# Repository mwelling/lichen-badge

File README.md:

# lichen-badge
Design files for the LICHEN Badge.

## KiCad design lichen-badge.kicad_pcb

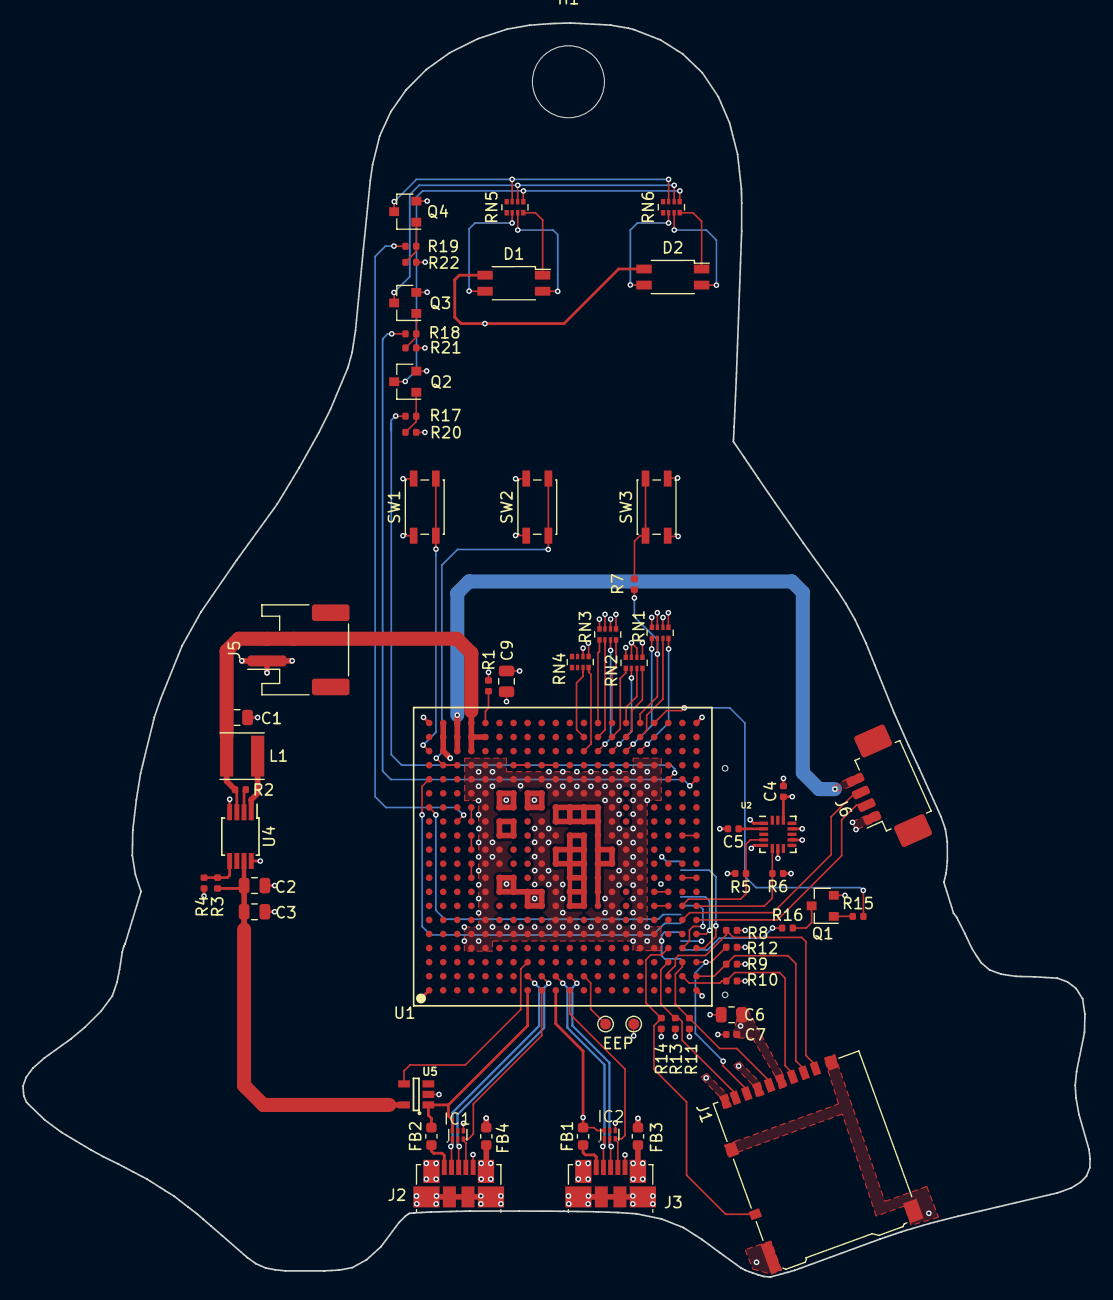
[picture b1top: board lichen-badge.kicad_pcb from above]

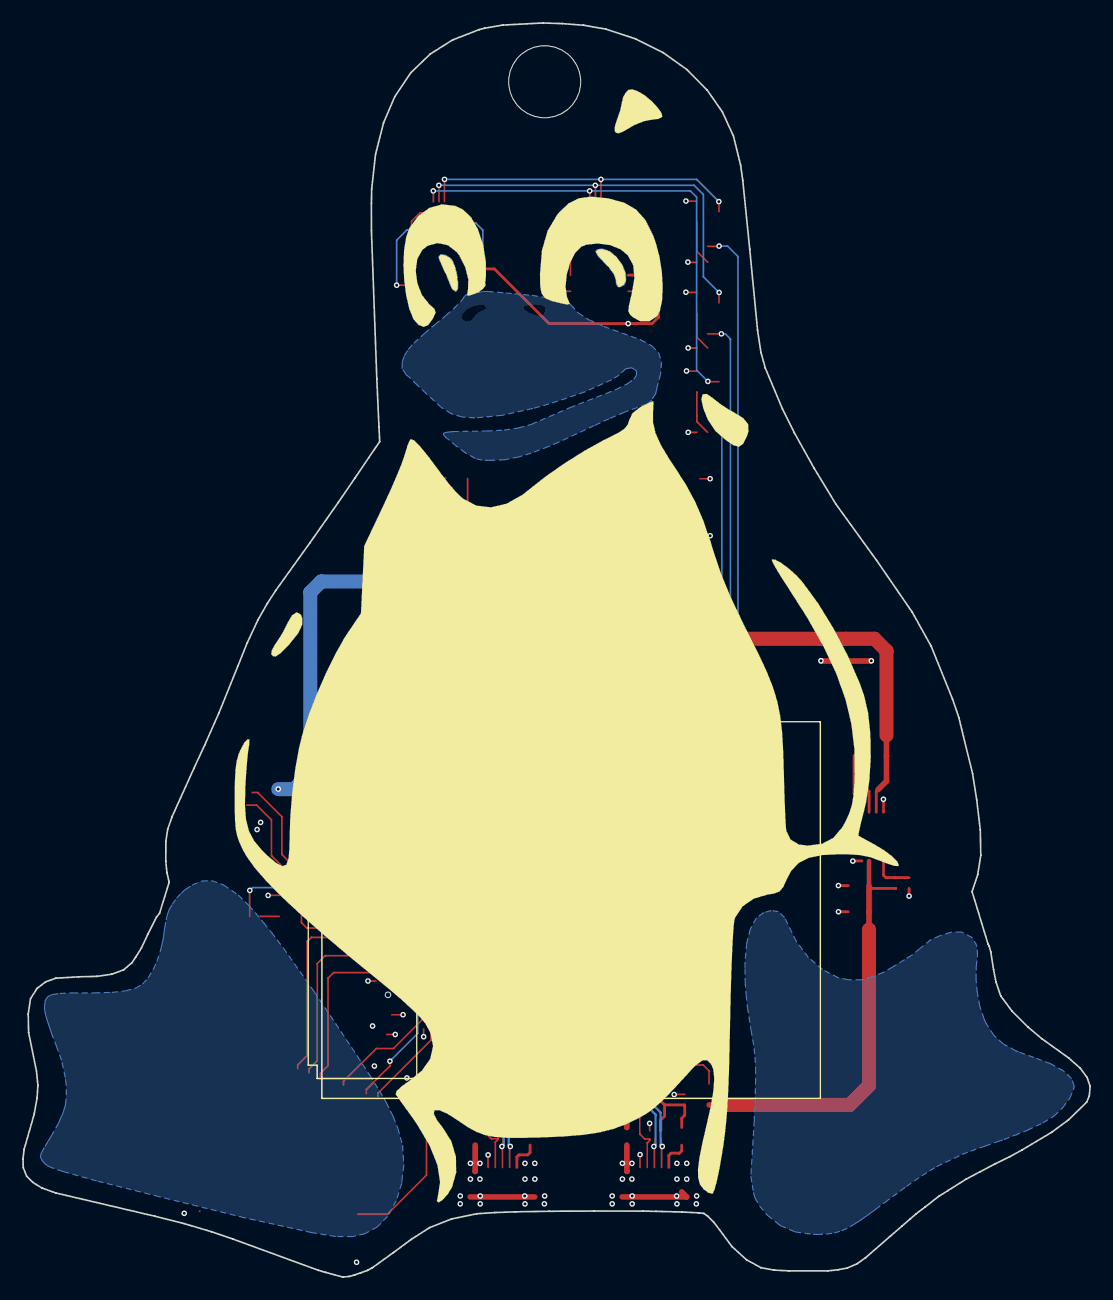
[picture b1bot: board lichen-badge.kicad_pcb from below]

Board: 4 copper layers, 96.3 x 113.2 mm, 66 parts (2 on the bottom side), 88 nets.

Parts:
C1, C2, C3: 22uF; C_0805_2012Metric
C4, C5, C7: .1uF; C_0402_1005Metric
C6: 10uF; C_0805_2012Metric
C9: 47uF; C_0805_2012Metric
D1, D2: LED_RABG; LED_SunLED_PLCC4_3.2x2.8mm_Reverse_Mount
FB1, FB2, FB3, FB4: Ferrite_Bead_Small; L_0603_1608Metric
H1: MountingHole; MountingHole_6.5mm
IC1, IC2: TPD4S012DRYR; SON-6(TI)-DRY
J1: Micro_SD_Card_Det; microSD_HC_Hirose_DM3AT-SF-PEJM5
J2, J3: USB_B_Micro; USB_Micro-B_Molex_47346-0001
J4, J7: TEST_1P; TestPoint_Pad_D1.0mm
J5: JST; JST_PH_S2B-PH-SM4-TB_1x02-1MP_P2.00mm_Horizontal
J6: Conn_01x04; Molex_PicoBlade_53261-0471_1x04-1MP_P1.25mm_Horizontal
L1: 2.2uH; L_Taiyo-Yuden_MD-4040
LOGO1: Logo_Open_Hardware_Small; tux-ghost
Q1, Q2, Q3, Q4: MMBT3904; SOT-23
R1: 10K; R_0402_1005Metric
R2, R3: 750K; R_0402_1005Metric
R4, R20, R21, R22: 100K; R_0402_1005Metric
R5, R6, R8, R9, R10, R11, R12, R13, R14, R17, R18, R19: 4.7K; R_0402_1005Metric
R7: 100; R_0402_1005Metric
R15: 470; R_0402_1005Metric
R16: 22; R_0402_1005Metric
RN1, RN2, RN3, RN4: 100K; R_Array_Convex_4x0402
RN5, RN6: 470; R_Array_Convex_4x0402
SW1: POWER; SW_SPST_EVQP2
SW2: RESET; SW_SPST_EVQP2
SW3: BOOT0; SW_SPST_EVQP2
U1: OSD335x-CSIP; BGA-400-1-27mm
U2: MMA8452QR1
U4: PAM2401SCADJ; MSOP-8_3x3mm_P0.65mm
U5: TPS2051C; SOT-23-5
X1: SPI-LCD-(1.8IN); LCD-(1.8IN)

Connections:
GND: C1.2, C2.2, C3.2, C4.2, C5.2, C6.2, C7.2, C9.2, FB3.2, FB4.2, IC1.4, IC2.4, J1.6, J1.9, J2.5, J3.5, J5.1, J6.1, J7.1, Q1.2, Q2.2, Q3.2, Q4.2, R1.2, R4.2, R20.2, R21.2, R22.2, RN1.5, RN1.6, RN2.6, RN2.7, RN2.8, RN3.5, RN3.6, RN3.7, RN3.8, RN4.5, RN4.6, SW1.1, SW2.1, SW3.2, U1.A1, U1.A20, U1.D4, U1.D5, U1.D15, U1.D16, U1.D17, U1.E4, U1.E5, U1.E6, U1.E7, U1.E8, U1.E9, U1.E10, U1.E11, U1.E12, U1.E13, U1.E14, U1.E15, U1.E16, U1.E17, U1.F5, U1.F10, U1.F11, U1.F16, U1.F17, U1.G5, U1.G16, U1.H5, U1.H16, U1.J5, U1.J9, U1.J10, U1.J11, U1.J12, U1.J13, U1.J16, U1.K5, U1.K6, U1.K7, U1.K8, U1.K9, U1.K12, U1.K15, U1.K16, U1.L5, U1.L6, U1.L15, U1.L16, U1.M5, U1.M15, U1.M16, U1.N5, U1.N6, U1.N15, U1.N16, U1.P5, U1.P6, U1.P7, U1.P8, U1.P9, U1.P12, U1.P13, U1.P14, U1.P15, U1.P16, U1.R5, U1.R9, U1.R10, U1.R11, U1.R12, U1.R16, U1.T4, U1.T5, U1.T6, U1.T7, U1.T8, U1.T9, U1.T10, U1.T11, U1.T12, U1.T13, U1.T14, U1.T15, U1.T16, U1.T17, U1.U4, U1.U5, U1.U15, U1.U16, U1.U17, U1.Y1, U1.Y20, U2.5, U2.7, U2.10, U2.12, U4.4, U4.8, U5.2, X1.2, X1.5, X1.13
GNDPWR: FB3.1, FB4.1, J1.11, J2.6, J3.6
I2C1_SCL: R5.2, U1.W7, U2.4
I2C1_SDA: R6.2, U1.Y7, U2.6
LCD_D0: RN1.4, U1.T18
LCD_D1: RN1.3, U1.T19
LCD_D2: R7.2, RN1.2, U1.T20
LCD_D3: RN1.1, U1.R18
LCD_D4: RN2.4, U1.R19
LCD_D5: RN2.3, U1.R20
LCD_D6: RN2.2, U1.P18
LCD_D7: RN2.1, U1.P19
LCD_D8: RN3.4, U1.P20
LCD_D9: RN3.3, U1.N18
LCD_D10: RN3.2, U1.N19
LCD_D11: RN3.1, U1.N20
LCD_D12: RN4.4, U1.M18
LCD_D13: RN4.3, U1.M19
LCD_PWM: R15.2, U1.U20
LCD_RESET: U1.A16, X1.6
LCD_RS: U1.A14, X1.7
MMC0_CD: J1.10, R14.2, U1.V4
MMC0_CLK: J1.5, R11.2, U1.W3
MMC0_CMD: J1.3, R10.2, U1.W2
MMC0_DAT0: J1.7, R12.2, U1.Y3
MMC0_DAT1: J1.8, R13.2, U1.V3
MMC0_DAT2: J1.1, R8.2, U1.V2
MMC0_DAT3: J1.2, R9.2, U1.Y2
unnamed: C5.1, U2.2
unnamed: D1.1, RN5.4
unnamed: D1.3, RN5.2
unnamed: D1.4, RN5.3
unnamed: D2.1, RN6.4
unnamed: D2.3, RN6.2
unnamed: D2.4, RN6.3
unnamed: FB1.1, J3.1
unnamed: FB2.1, J2.1
unnamed: J4.1, U1.M2
unnamed: L1.2, U4.1
unnamed: Q1.1, R15.1
unnamed: Q1.3, R16.2
unnamed: Q2.1, R17.1, R20.1
unnamed: Q2.3, RN5.5, RN6.5
unnamed: Q3.1, R18.1, R21.1
unnamed: Q3.3, RN5.6, RN6.6
unnamed: Q4.1, R19.1, R22.1
unnamed: Q4.3, RN5.7, RN6.7
unnamed: R1.1, U1.E20
unnamed: R2.2, U4.2
unnamed: R3.2, R4.1, U4.5
unnamed: R7.1, SW3.1
unnamed: R16.1, X1.3
unnamed: SW1.2, U1.A18
unnamed: SW2.2, U1.B17, U1.C17
unnamed: U1.D9, U1.D10
unnamed: U1.D11, U1.D12
unnamed: U1.D13, U1.D14
unnamed: U1.G17, U1.H17
unnamed: U1.J17, U1.K17
unnamed: U1.U7, U1.V7
unnamed: U1.U8, U1.V8
unnamed: U1.W9, U1.Y9
unnamed: U1.W12, U1.Y12
PWM_BLUE: R19.2, U1.C13
PWM_GREEN: R18.2, U1.Y16
PWM_RED: R17.2, U1.V16
SPI0_MOSI: U1.W4, X1.8
SPI0_SCLK: U1.Y5, X1.9
SPI0_nCS0: U1.Y4, X1.12
SYS_VDD1_3P3V: C4.1, C6.1, C7.1, J1.4, R5.1, R6.1, R8.1, R9.1, R10.1, R11.1, R12.1, R13.1, R14.1, RN1.7, RN1.8, RN2.5, U1.F8, U1.F9, U1.G8, U1.G9, U1.H7, U1.H8, U1.H14, U1.H15, U1.J7, U1.J8, U1.J14, U1.J15, U2.1, U2.14, X1.4, X1.10, X1.11
SYS_VDD2_3P3V: U1.F12, U1.F13, U1.G12, U1.G13
SYS_VDD3_3P3V: U1.K10, U1.K11, U1.L7, U1.L8, U1.L9, U1.L10, U1.L11, U1.L12, U1.M7, U1.M8, U1.M9, U1.M10, U1.M11, U1.M12
SYS_VDD_1P8V: U1.K13, U1.K14, U1.L13, U1.L14, U1.M13, U1.M14, U1.N7, U1.N8, U1.N9, U1.N10, U1.N11, U1.N12, U1.N13, U1.N14, U1.P10, U1.P11
SYS_VOUT: C9.1, D1.2, D2.2, U1.F14, U1.F15, U1.G14, U1.G15
UART0_RXD: J6.2, U1.Y6
UART0_TXD: J6.3, U1.W6
USB0_D+: IC2.2, J3.3, U1.L2
USB0_D-: IC2.1, J3.2, U1.K2
USB0_ID: IC2.3, J3.4, U1.L1
USB0_VBUS: FB1.2, IC2.6, U1.B18, U1.B19, U1.B20, U1.K1
USB1_D+: IC1.2, J2.3, U1.J2
USB1_D-: IC1.1, J2.2, U1.H2
USB1_DRVVBUS: U1.H3, U5.4
USB1_ID: IC1.3, J2.4, U1.J1
USB1_VBUS: FB2.2, IC1.6, U1.H1, U5.1
VBAT: C1.1, J5.2, L1.1, R2.1, U1.D18, U1.D19, U1.D20, U1.E19, U4.3
VBOOST: C2.1, C3.1, R3.1, U4.7, U5.5
VIN_AC: J6.4, U1.C18, U1.C19, U1.C20

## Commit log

2019-03-05 Update schematic for Octavo review
2019-03-24 Updates per review from Octavo
2019-07-29 Design released to OSHPark
    Hope it works. :)
2019-07-29 Put some images on the README
2019-07-29 Update schematic PDF
2019-08-01 Add BOM for the design
2019-11-08 Update BOM for pretty formatting
2019-11-12 Add gerbers to repo
    For anyone looking to make a board or stencil.
